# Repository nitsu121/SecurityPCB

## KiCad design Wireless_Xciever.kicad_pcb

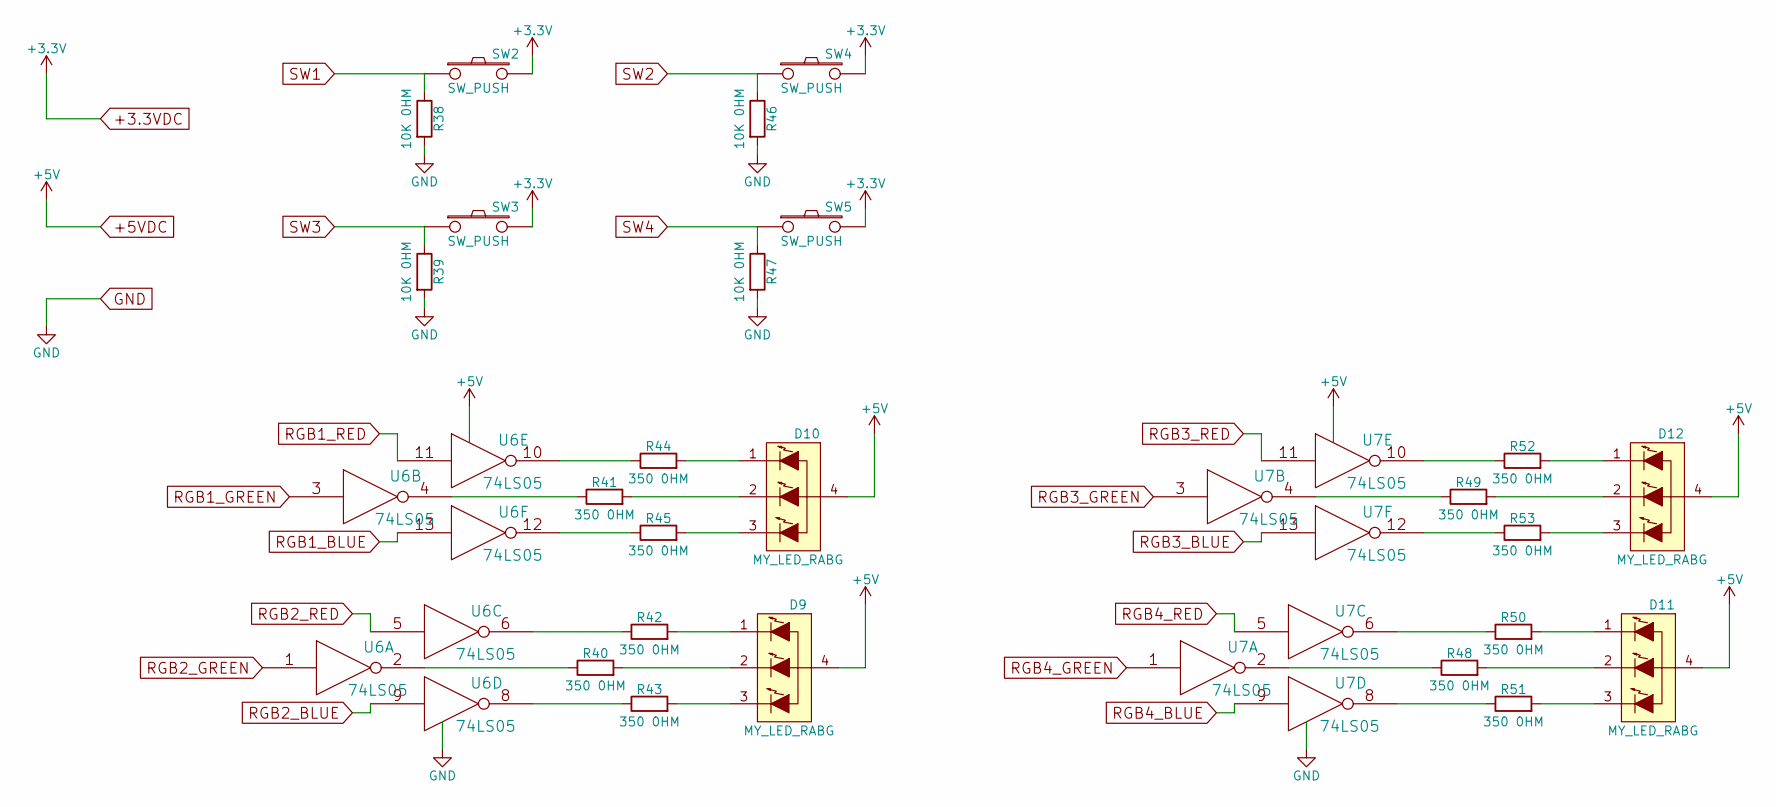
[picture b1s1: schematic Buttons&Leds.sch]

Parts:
D9, D10, D11, D12: MY_LED_RABG; MY_RGB_LED
R38, R39, R46, R47: 10K 0HM; R_0402
R40, R41, R42, R43, R44, R45, R48, R49, R50, R51, R52, R53: 350 0HM; R_0603
SW2, SW3, SW4, SW5: SW_PUSH; SW_SPST_EVPBF
U6, U7: 74LS05; SOIC-14_3.9x8.7mm_Pitch1.27mm

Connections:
+3.3VDC: SW2.2, SW3.2, SW4.2, SW5.2; also elsewhere on the board
+5VDC: D9.4 (COMMON_ANODE), D10.4 (COMMON_ANODE), D11.4 (COMMON_ANODE), D12.4 (COMMON_ANODE), U6.14 (VCC), U7.14 (VCC); also elsewhere on the board
GND: R38.2, R39.2, R46.2, R47.2, U6.7 (GND), U7.7 (GND); also elsewhere on the board
unnamed: D9.1 (RED_CATHODE), R42.2
unnamed: D9.2 (GREEN_CATHODE), R40.2
unnamed: D9.3 (BLUE_CATHODE), R43.2
unnamed: D10.1 (RED_CATHODE), R44.2
unnamed: D10.2 (GREEN_CATHODE), R41.2
unnamed: D10.3 (BLUE_CATHODE), R45.2
unnamed: D11.1 (RED_CATHODE), R50.2
unnamed: D11.2 (GREEN_CATHODE), R48.2
unnamed: D11.3 (BLUE_CATHODE), R51.2
unnamed: D12.1 (RED_CATHODE), R52.2
unnamed: D12.2 (GREEN_CATHODE), R49.2
unnamed: D12.3 (BLUE_CATHODE), R53.2
unnamed: R40.1, U6.2
unnamed: R41.1, U6.4
unnamed: R42.1, U6.6
unnamed: R43.1, U6.8
unnamed: R44.1, U6.10
unnamed: R45.1, U6.12
unnamed: R48.1, U7.2
unnamed: R49.1, U7.4
unnamed: R50.1, U7.6
unnamed: R51.1, U7.8
unnamed: R52.1, U7.10
unnamed: R53.1, U7.12
RGB1_BLUE: U6.13; also elsewhere on the board
RGB1_GREEN: U6.3; also elsewhere on the board
RGB1_RED: U6.11; also elsewhere on the board
RGB2_BLUE: U6.9; also elsewhere on the board
RGB2_GREEN: U6.1; also elsewhere on the board
RGB2_RED: U6.5; also elsewhere on the board
RGB3_BLUE: U7.13; also elsewhere on the board
RGB3_GREEN: U7.3; also elsewhere on the board
RGB3_RED: U7.11; also elsewhere on the board
RGB4_BLUE: U7.9; also elsewhere on the board
RGB4_GREEN: U7.1; also elsewhere on the board
RGB4_RED: U7.5; also elsewhere on the board
SW1: R38.1, SW2.1; also elsewhere on the board
SW2: R46.1, SW4.1; also elsewhere on the board
SW3: R39.1, SW3.1; also elsewhere on the board
SW4: R47.1, SW5.1; also elsewhere on the board

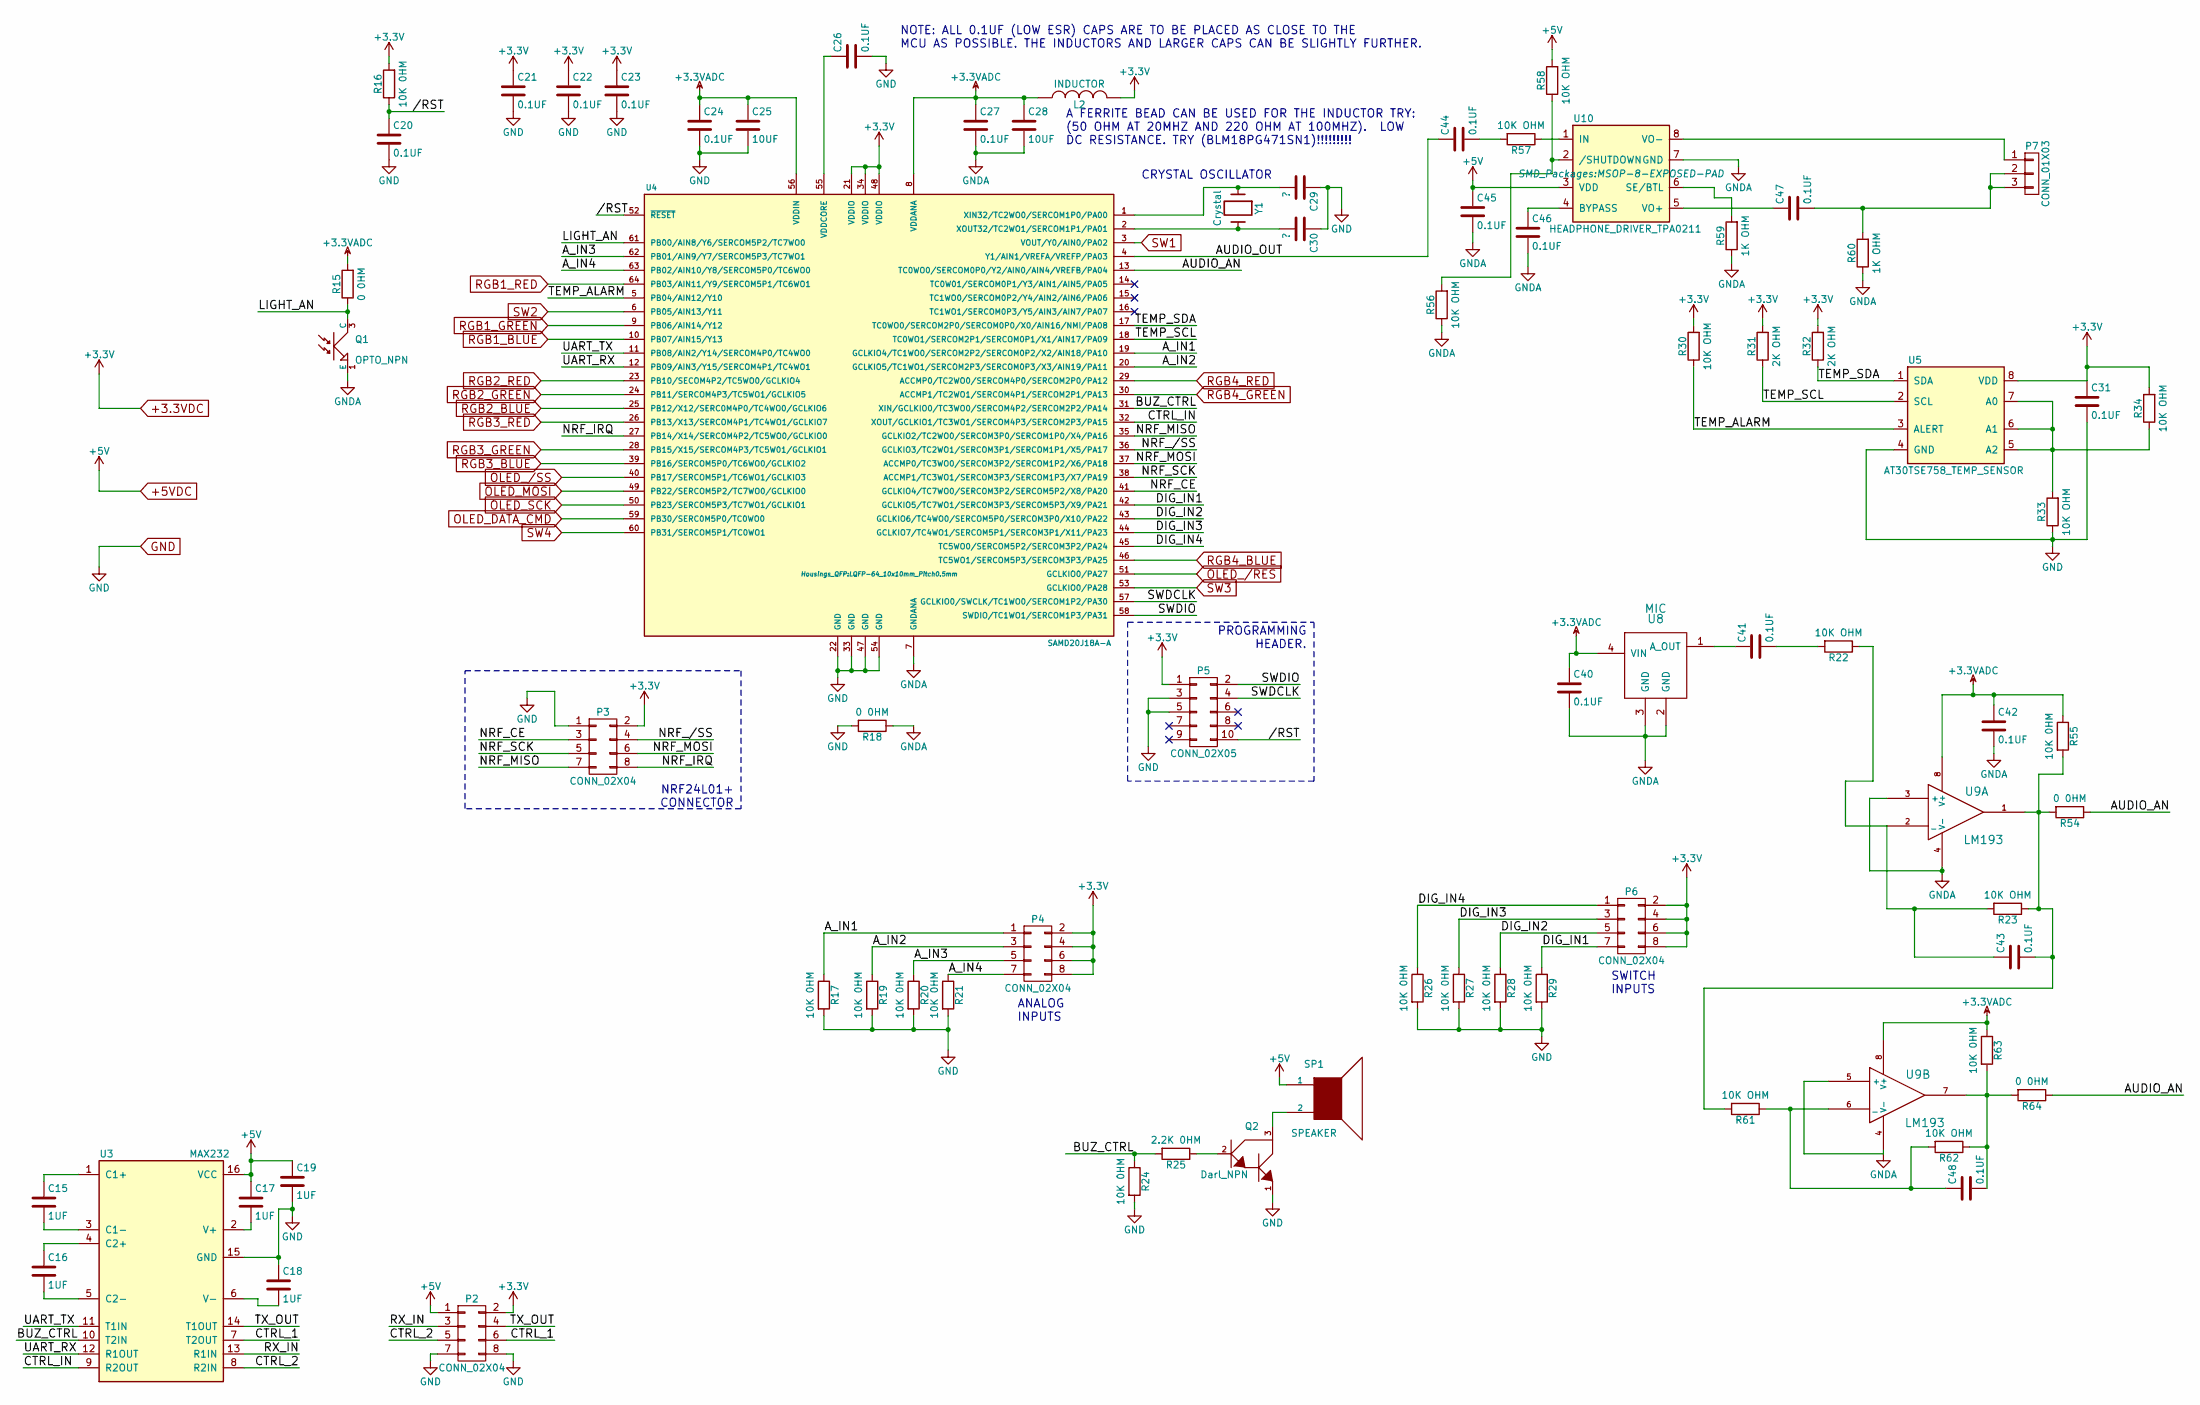
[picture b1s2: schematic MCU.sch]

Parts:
C15, C16, C17, C18, C19: 1UF; C_0603
C20, C21, C22, C23, C24, C26, C27, C31, C40, C41, C42, C43, C44, C45, C46, C47, C48: 0.1UF; C_0402
C25: 10UF; C_0402
C28: 10UF; C_0603
C29, C30: ?; C_0402
L2: INDUCTOR; R_0603
P2, P3, P4, P6: CONN_02X04; My_0.1_5X2RowConnector
P5: CONN_02X05; My_Programmer_Connector_5x2row
P7: CONN_01X03; MY_AUDIO_JACK
Q1: OPTO_NPN; My_light_sensor_4X2
Q2: Darl_NPN; SOT-23
R15: 0 0HM; R_0603
R16, R17, R19, R20, R21, R24, R26, R27, R28, R29, R55, R63: 10K 0HM; R_0402
R18, R54, R64: 0 0HM; R_0402
R22, R23, R30, R33, R34, R56, R57, R58, R61, R62: 10K OHM; R_0402
R25: 2.2K 0HM; R_0402
R31, R32: 2K OHM; R_0402
R59, R60: 1K OHM; R_0402
SP1: SPEAKER; My_Buzzer_12.8X12.8
U3: MAX232; SO-16-N
U4: SAMD20J18A-A; LQFP-64_10x10mm_Pitch0.5mm
U5: AT30TSE758_TEMP_SENSOR; SOIC-8_3.9x4.9mm_Pitch1.27mm
U8: MIC; MY_MIC
U9: LM193; SOIC-8-N
U10: HEADPHONE_DRIVER_TPA0211; MSOP-8-EXPOSED-PAD
Y1: Crystal; Crystal_Round_Vertical_3mm

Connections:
+3.3VADC: C24.1, C25.1, C27.1, C28.1, C40.1, C42.1, L2.1, R15.2, R55.1, R63.1, U4.8 (VDDANA), U4.56 (VDDIN), U8.4 (VIN), U9.8 (V+)
+3.3VDC: C21.1, C22.1, C23.1, C31.1, L2.2, P2.2, P3.2, P4.2, P4.4, P4.6, P4.8, P5.1, P6.2, P6.4, P6.6, P6.8, R16.2, R30.2, R31.2, R32.2, R34.2, U4.21 (VDDIO), U4.34 (VDDIO), U4.48 (VDDIO), U5.8 (VDD); also elsewhere on the board
+5VDC: C17.1, C19.1, C45.1, P2.1, R58.2, SP1.1, U3.16 (VCC), U10.3 (VDD); also elsewhere on the board
/MCUSheet//RST: C20.1, P5.10, R16.1, U4.52 (~RESET~)
/MCUSheet/AUDIO_AN: R54.1, R64.1, U4.13 (TC0WO0/SERCOM0P0/Y2/AIN0/AIN4/VREFB/PA04)
/MCUSheet/AUDIO_OUT: C44.1, U4.4 (Y1/AIN1/VREFA/VREFP/PA03)
/MCUSheet/A_IN1: P4.1, R17.1, U4.19 (GCLKIO4/TC1WO0/SERCOM2P2/SERCOM0P2/X2/A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)
/MCUSheet/A_IN2: P4.3, R19.1, U4.20 (GCLKIO5/TC1WO1/SERCOM2P3/SERCOM0P3/X3/A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)
/MCUSheet/A_IN3: P4.5, R20.1, U4.62 (PB01/AIN9/Y7/SERCOM5P3/TC7WO1)
/MCUSheet/A_IN4: P4.7, R21.1, U4.63 (PB02/AIN10/Y8/SERCOM5P0/TC6WO0)
/MCUSheet/BUZ_CTRL: R24.1, R25.2, U3.10 (T2IN), U4.31 (XIN/GCLKIO0/TC3WO0/SERCOM4P2/SERCOM2P2/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)
/MCUSheet/CTRL_1: P2.6, U3.7 (T2OUT)
/MCUSheet/CTRL_2: P2.5, U3.8 (R2IN)
/MCUSheet/CTRL_IN: U3.9 (R2OUT), U4.32 (XOUT/GCLKIO1/TC3WO1/SERCOM4P3/SERCOM2P3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)
/MCUSheet/DIG_IN1: P6.7, R29.1, U4.42 (GCLKIO5/TC7WO1/SERCOM3P3/SERCOM5P3/X9/P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)
/MCUSheet/DIG_IN2: P6.5, R28.1, U4.43 (GCLKIO6/TC4WO0/SERCOM5P0/SERCOM3P0/X10/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)
/MCUSheet/DIG_IN3: P6.3, R27.1, U4.44 (GCLKIO7/TC4WO1/SERCOM5P1/SERCOM3P1/X11/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)
/MCUSheet/DIG_IN4: P6.1, R26.1, U4.45 (TC5WO0/SERCOM5P2/SERCOM3P2/PA24)
/MCUSheet/LIGHT_AN: Q1.3 (C), R15.1, U4.61 (PB00/AIN8/Y6/SERCOM5P2/TC7WO0)
/MCUSheet/NRF_/SS: P3.4, U4.36 (GCLKIO3/TC2WO1/SERCOM3P1/SERCOM1P1/X5/P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)
/MCUSheet/NRF_CE: P3.3, U4.41 (GCLKIO4/TC7WO0/SERCOM3P2/SERCOM5P2/X8/P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)
/MCUSheet/NRF_IRQ: P3.8, U4.27 (PB14/X14/SERCOM4P2/TC5WO0/GCLKIO0)
/MCUSheet/NRF_MISO: P3.7, U4.35 (GCLKIO2/TC2WO0/SERCOM3P0/SERCOM1P0/X4/P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)
/MCUSheet/NRF_MOSI: P3.6, U4.37 (ACCMP0/TC3WO0/SERCOM3P2/SERCOM1P2/X6/PA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)
/MCUSheet/NRF_SCK: P3.5, U4.38 (ACCMP1/TC3WO1/SERCOM3P3/SERCOM1P3/X7/PA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)
/MCUSheet/RX_IN: P2.3, U3.13 (R1IN)
/MCUSheet/SWDCLK: P5.4, U4.57 (GCLKIO0/SWCLK/TC1WO0/SERCOM1P2/PA30)
/MCUSheet/SWDIO: P5.2, U4.58 (SWDIO/TC1WO1/SERCOM1P3/PA31)
/MCUSheet/TEMP_ALARM: R30.1, U4.5 (PB04/AIN12/Y10), U5.3 (ALERT)
/MCUSheet/TEMP_SCL: R31.1, U4.18 (TC0WO1/SERCOM2P1/SERCOM0P1/X1/AIN17/PA09), U5.2 (SCL)
/MCUSheet/TEMP_SDA: R32.1, U4.17 (TC0WO0/SERCOM2P0/SERCOM0P0/X0/AIN16/NMI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), U5.1 (SDA)
/MCUSheet/TX_OUT: P2.4, U3.14 (T1OUT)
/MCUSheet/UART_RX: U3.12 (R1OUT), U4.12 (PB09/AIN3/Y15/SERCOM4P1/TC4WO1)
/MCUSheet/UART_TX: U3.11 (T1IN), U4.11 (PB08/AIN2/Y14/SERCOM4P0/TC4WO0)
GND: C18.1, C19.2, C20.2, C21.2, C22.2, C23.2, C24.2, C25.2, C26.2, C29.1, C30.1, C31.2, P2.7, P2.8, P3.1, P5.3, P5.5, Q2.1, R17.2, R18.2, R19.2, R20.2, R21.2, R24.2, R26.2, R27.2, R28.2, R29.2, R33.1, U3.15 (GND), U4.22 (GND), U4.33 (GND), U4.47 (GND), U4.54 (GND), U5.4 (GND); also elsewhere on the board
GNDA: C27.2, C28.2, C40.2, C42.2, C45.2, C46.2, Q1.1 (E), R18.1, R56.1, R59.1, R60.1, U4.7 (GNDANA), U8.2 (GND), U8.3 (GND), U9.3 (+), U9.4 (V-), U9.5 (+), U10.7 (GND)
unnamed: C15.1, U3.1 (C1+)
unnamed: C15.2, U3.3 (C1-)
unnamed: C16.1, U3.4 (C2+)
unnamed: C16.2, U3.5 (C2-)
unnamed: C17.2, U3.2 (V+)
unnamed: C18.2, U3.6 (V-)
unnamed: C26.1, U4.55 (VDDCORE)
unnamed: C29.2, U4.1 (XIN32/TC2WO0/SERCOM1P0/PA00), Y1.1
unnamed: C30.2, U4.2 (XOUT32/TC2WO1/SERCOM1P1/PA01), Y1.2
unnamed: C41.1, U8.1 (A_OUT)
unnamed: C41.2, R22.2
unnamed: C43.1, R22.1, R23.2, U9.2 (_)
unnamed: C43.2, R23.1, R54.2, R55.2, R61.2, U9.1
unnamed: C44.2, R57.2
unnamed: C46.1, U10.4 (BYPASS)
unnamed: C47.1, U10.5 (VO+)
unnamed: C47.2, P7.2, P7.3, R60.2
unnamed: C48.1, R61.1, R62.2, U9.6 (_)
unnamed: C48.2, R62.1, R63.2, R64.2, U9.7
unnamed: P7.1, U10.8 (VO-)
unnamed: Q2.2, R25.1
unnamed: Q2.3, SP1.2
unnamed: R33.2, R34.1, U5.5 (A2), U5.6 (A1), U5.7 (A0)
unnamed: R56.2, R58.1, U10.2 (/SHUTDOWN)
unnamed: R57.1, U10.1 (IN)
unnamed: R59.2, U10.6 (SE/BTL)
OLED_/RES: U4.51 (GCLKIO0/PA27); also elsewhere on the board
OLED_/SS: U4.40 (PB17/SERCOM5P1/TC6WO1/GCLKIO3); also elsewhere on the board
OLED_DATA_CMD: U4.59 (PB30/SERC0M5P0/TC0WO0); also elsewhere on the board
OLED_MOSI: U4.49 (PB22/SERCOM5P2/TC7WO0/GCLKIO0); also elsewhere on the board
OLED_SCK: U4.50 (PB23/SERCOM5P3/TC7WO1/GCLKIO1); also elsewhere on the board
RGB1_BLUE: U4.10 (PB07/AIN15/Y13); also elsewhere on the board
RGB1_GREEN: U4.9 (PB06/AIN14/Y12); also elsewhere on the board
RGB1_RED: U4.64 (PB03/AIN11/Y9/SERCOM5P1/TC6WO1); also elsewhere on the board
RGB2_BLUE: U4.25 (PB12/X12/SERC0M4P0/TC4WO0/GCLKIO6); also elsewhere on the board
RGB2_GREEN: U4.24 (PB11/SERCOM4P3/TC5WO1/GCLKIO5); also elsewhere on the board
RGB2_RED: U4.23 (PB10/SECOM4P2/TC5WO0/GCLKIO4); also elsewhere on the board
RGB3_BLUE: U4.39 (PB16/SERCOM5P0/TC6WO0/GCLKIO2); also elsewhere on the board
RGB3_GREEN: U4.28 (PB15/X15/SERCOM4P3/TC5W01/GCLKIO1); also elsewhere on the board
RGB3_RED: U4.26 (PB13/X13/SERCOM4P1/TC4WO1/GCLKIO7); also elsewhere on the board
RGB4_BLUE: U4.46 (TC5WO1/SERCOM5P3/SERCOM3P3/PA25); also elsewhere on the board
RGB4_GREEN: U4.30 (ACCMP1/TC2WO1/SERCOM4P1/SERCOM2P1/PA13); also elsewhere on the board
RGB4_RED: U4.29 (ACCMP0/TC2WO0/SERCOM4P0/SERCOM2P0/PA12); also elsewhere on the board
SW1: U4.3 (VOUT/Y0/AIN0/PA02); also elsewhere on the board
SW2: U4.6 (PB05/AIN13/Y11); also elsewhere on the board
SW3: U4.53 (GCLKIO0/PA28); also elsewhere on the board
SW4: U4.60 (PB31/SERCOM5P1/TC0WO1); also elsewhere on the board

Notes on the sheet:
NOTE: ALL 0.1UF (LOW ESR) CAPS ARE TO BE PLACED AS CLOSE TO THE MCU AS POSSIBLE. THE INDUCTORS AND LARGER CAPS CAN BE SLIGHTLY FURTHER.
A FERRITE BEAD CAN BE USED FOR THE INDUCTOR TRY: (50 OHM AT 20MHZ AND 220 OHM AT 100MHZ). LOW DC RESISTANCE. TRY (BLM18PG471SN1)!!!!!!!!!
PROGRAMMING HEADER.
CRYSTAL OSCILLATOR
NRF24L01+ CONNECTOR
SWITCH INPUTS
ANALOG INPUTS

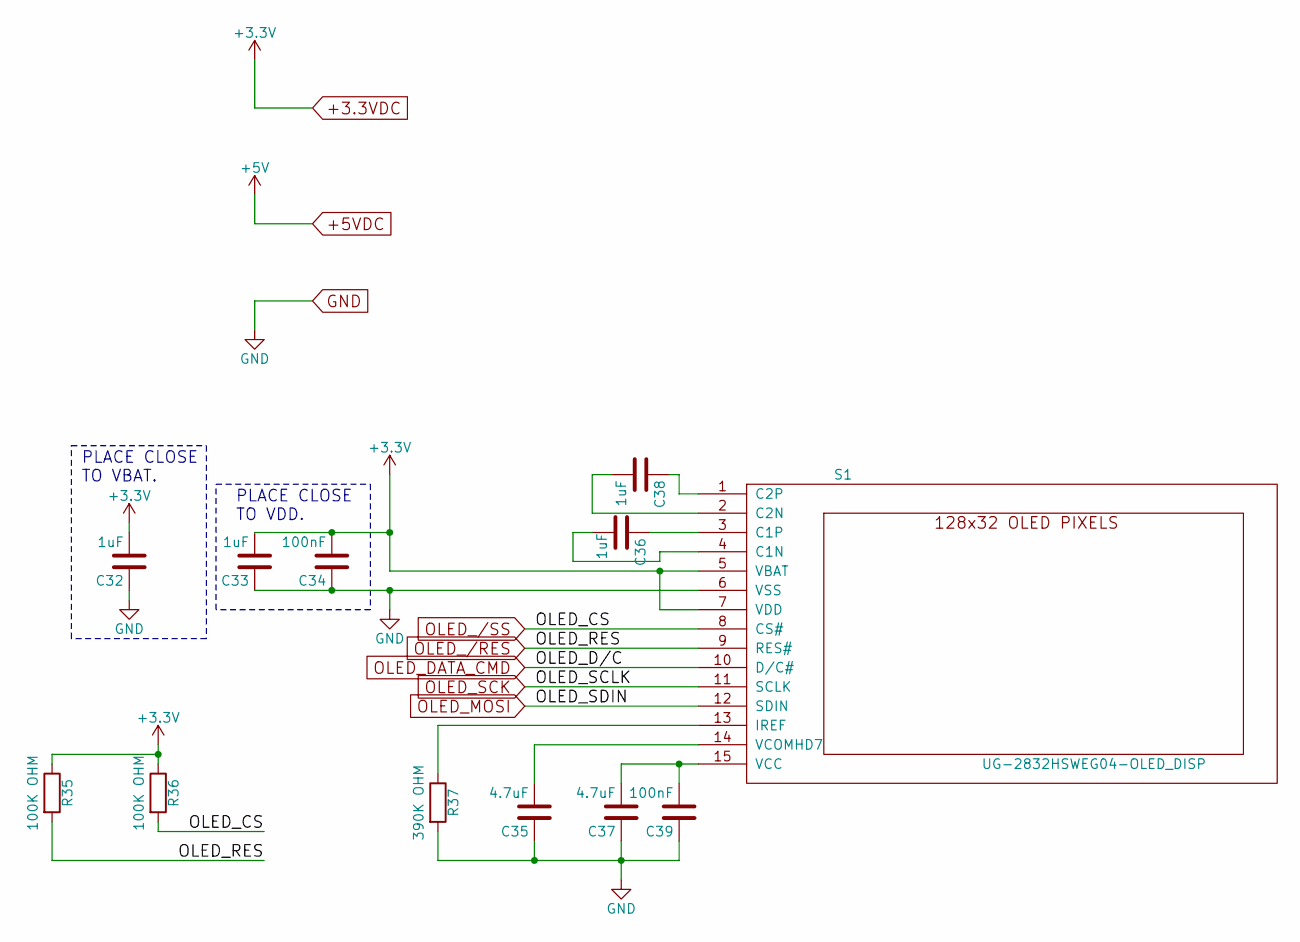
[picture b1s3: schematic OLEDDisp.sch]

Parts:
C32, C33, C36, C38: 1uF; C_0402
C34, C39: 100nF; C_0402
C35, C37: 4.7uF; C_0402
R35, R36: 100K OHM; R_0402
R37: 390K OHM; R_0402
S1: UG-2832HSWEG04-OLED_DISP; MY_OLED_UG-2832hsweg04

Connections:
+3.3VDC: C32.2, C33.2, C34.2, R35.1, R36.1, S1.5 (VBAT), S1.7 (VDD); also elsewhere on the board
GND: C32.1, C33.1, C34.1, C35.1, C37.1, C39.1, R37.2, S1.6 (VSS); also elsewhere on the board
unnamed: C35.2, S1.14 (VCOMHD7)
unnamed: C36.1, S1.3 (C1P)
unnamed: C36.2, S1.4 (C1N)
unnamed: C37.2, C39.2, S1.15 (VCC)
unnamed: C38.1, S1.1 (C2P)
unnamed: C38.2, S1.2 (C2N)
unnamed: R37.1, S1.13 (IREF)
OLED_/RES: R35.2, S1.9 (RES#); also elsewhere on the board
OLED_/SS: R36.2, S1.8 (CS#); also elsewhere on the board
OLED_DATA_CMD: S1.10 (D/C#); also elsewhere on the board
OLED_MOSI: S1.12 (SDIN); also elsewhere on the board
OLED_SCK: S1.11 (SCLK); also elsewhere on the board

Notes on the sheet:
PLACE CLOSE TO VDD.
PLACE CLOSE TO VBAT.

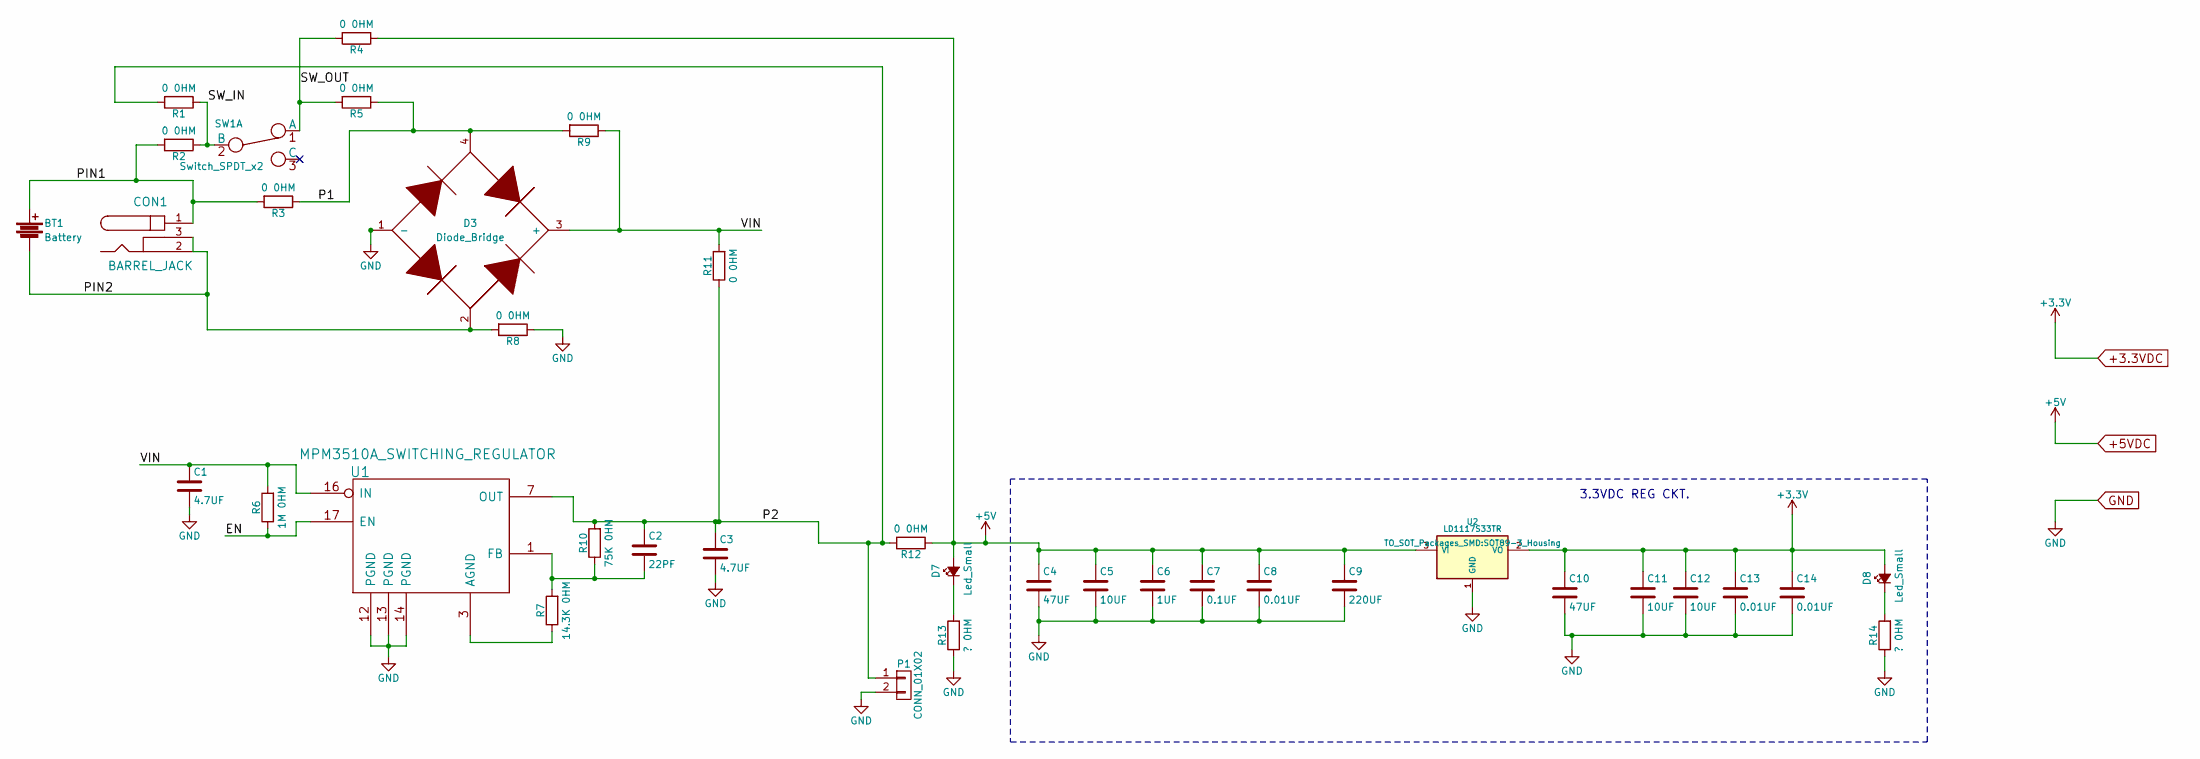
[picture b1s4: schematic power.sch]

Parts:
BT1: Battery; Connectors_JST_B2B-PH-K
C1, C3: 4.7UF; C_0603
C2: 22PF; C_0402
C4, C10: 47UF; C_0805
C5: 10UF; C_0603
C6: 1UF; C_0402
C7: 0.1UF; C_0402
C8, C13, C14: 0.01UF; C_0402
C9: 220UF; C_1210
C11, C12: 10UF; C_0402
CON1: BARREL_JACK
D3: Diode_Bridge; MY_NEW_FULL_BRIDGE_RECTIFIER
D7, D8: Led_Small; MY_LED-1.6X0.8
P1: CONN_01X02; Pin_Header_Straight_1x02
R1, R2, R3, R4, R5, R8, R9, R11, R12: 0 0HM; R_0603
R6: 1M 0HM; R_0603
R7: 14.3K 0HM; R_0603
R10: 75K 0HM; R_0603
R13: ? 0HM; R_0603
R14: ? 0HM; R_0402
SW1: Switch_SPDT_x2; SW_Micro_SPST
U1: MPM3510A_SWITCHING_REGULATOR; MPM3510A
U2: LD1117S33TR; SOT89-3_Housing

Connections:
+3.3VDC: C10.1, C11.1, C12.1, C13.1, C14.1, D8.2 (A), U2.2 (VO); also elsewhere on the board
+5VDC: C4.1, C5.1, C6.1, C7.1, C8.1, C9.1, D7.2 (A), R4.1, R12.1, U2.3 (VI); also elsewhere on the board
/powerSheet/EN: R6.1, U1.17 (EN)
/powerSheet/P1: D3.4, R3.1, R5.1, R9.2
/powerSheet/P2: C2.1, C3.1, P1.1, R1.2, R10.2, R11.1, R12.2, U1.7 (OUT)
/powerSheet/PIN1: BT1.1, CON1.1, R2.2, R3.2
/powerSheet/PIN2: BT1.2, CON1.2, CON1.3, D3.2, R8.2
/powerSheet/SW_IN: R1.1, R2.1, SW1.2 (B)
/powerSheet/SW_OUT: R4.2, R5.2, SW1.1 (A)
/powerSheet/VIN: C1.1, D3.3 (+), R6.2, R9.1, R11.2, U1.16 (IN)
GND: C1.2, C3.2, C4.2, C5.2, C6.2, C7.2, C8.2, C9.2, C10.2, C11.2, C12.2, C13.2, C14.2, D3.1 (-), P1.2, R8.1, R13.1, R14.1, U1.12 (PGND), U1.13 (PGND), U1.14 (PGND), U2.1 (GND); also elsewhere on the board
unnamed: C2.2, R7.2, R10.1, U1.1 (FB)
unnamed: D7.1 (K), R13.2
unnamed: D8.1 (K), R14.2
unnamed: R7.1, U1.3 (AGND)

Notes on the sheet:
3.3VDC REG CKT.

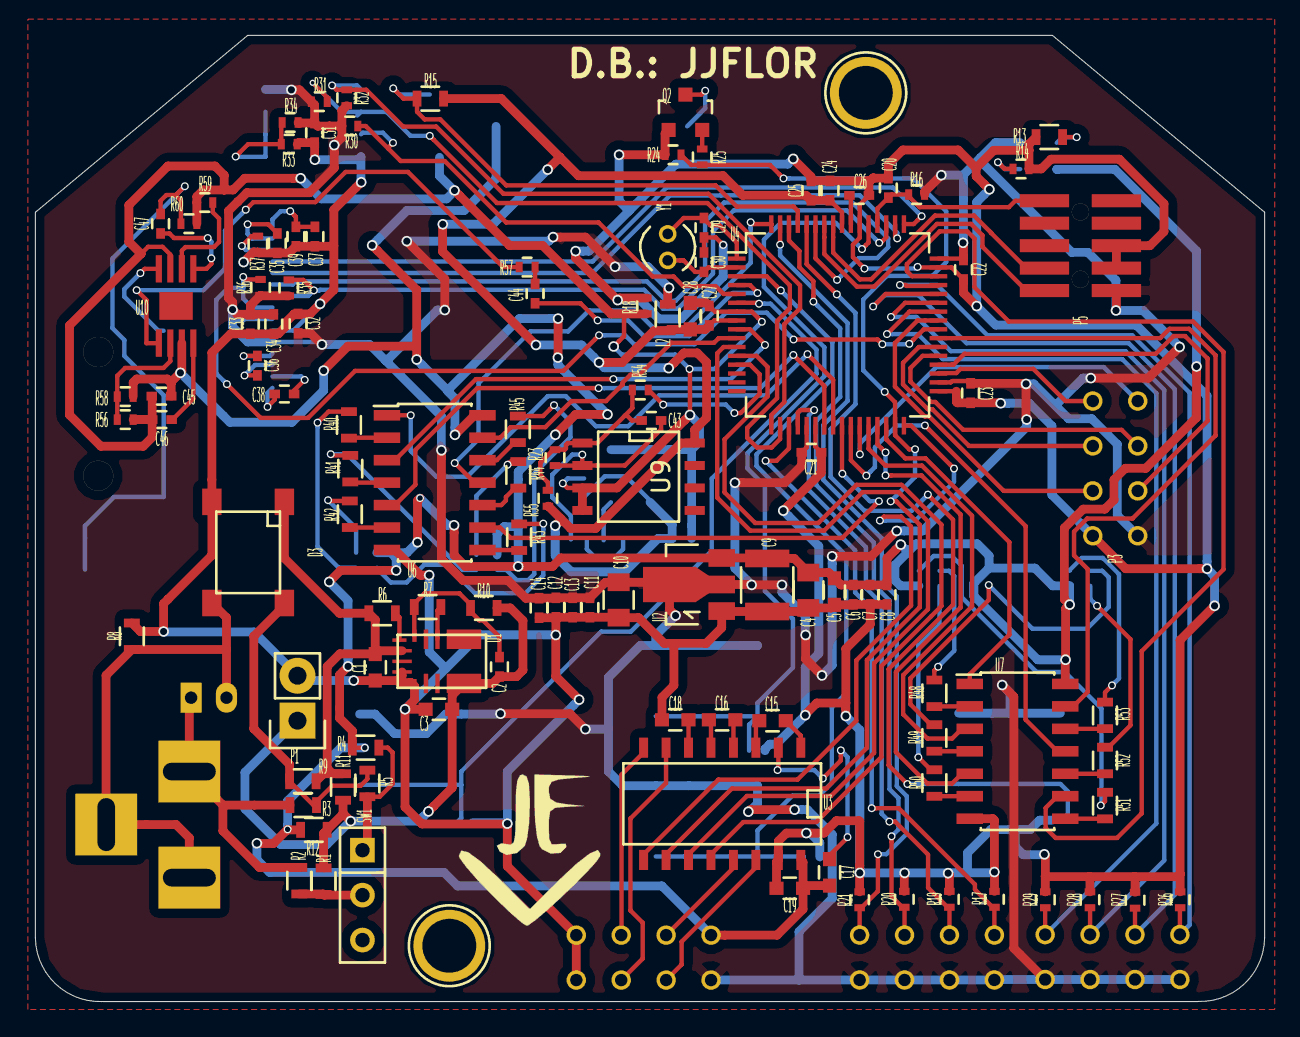
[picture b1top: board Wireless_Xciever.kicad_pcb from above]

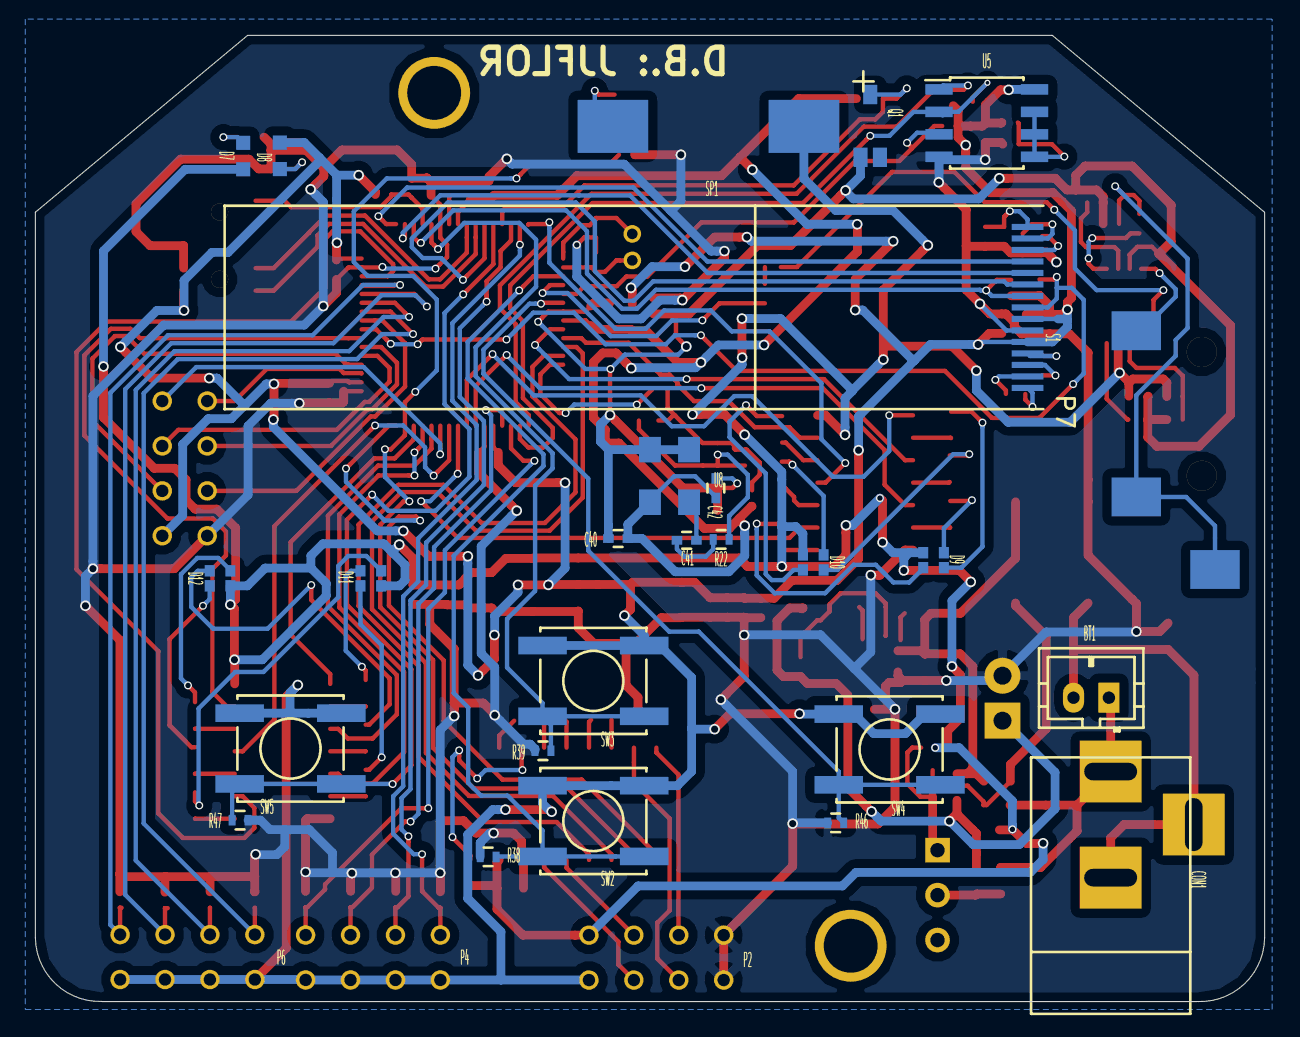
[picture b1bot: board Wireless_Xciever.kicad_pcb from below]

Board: 2 copper layers, 69.5 x 54.6 mm, 144 parts (29 on the bottom side), 124 nets.
